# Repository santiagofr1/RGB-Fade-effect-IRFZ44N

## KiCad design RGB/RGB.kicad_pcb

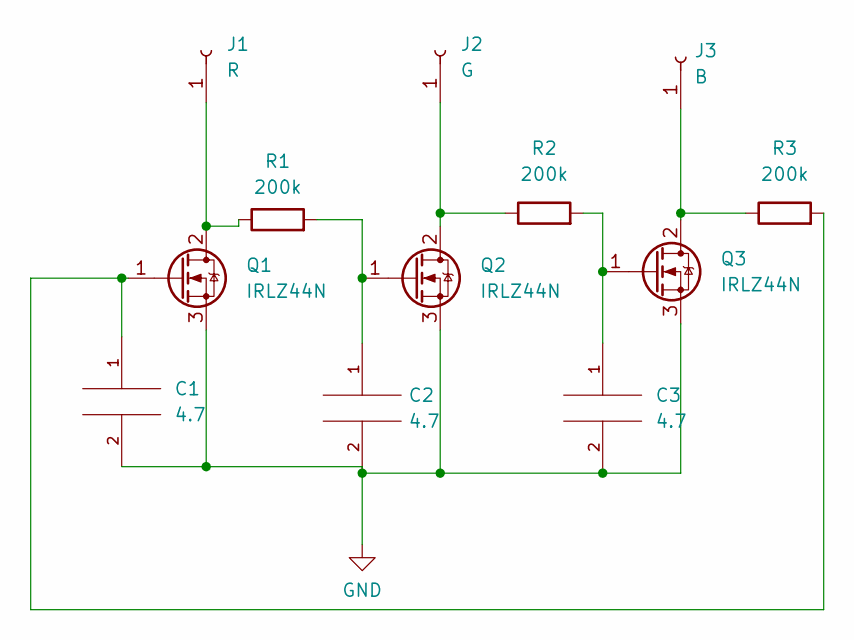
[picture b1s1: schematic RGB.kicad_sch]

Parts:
C1, C2, C3: 4.7; CP_Radial_D5.0mm_P2.00mm
J1: R; Pin_D1.0mm_L10.0mm
J2: G; Pin_D1.0mm_L10.0mm
J3: B; Pin_D1.0mm_L10.0mm
Q1, Q2, Q3: IRLZ44N; TO-220-3_Vertical
R1, R2, R3: 200k; R_Axial_DIN0207_L6.3mm_D2.5mm_P7.62mm_Horizontal

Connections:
GND: C1.2, C2.2, C3.2, Q1.3 (S), Q2.3 (S), Q3.3 (S); also elsewhere on the board
unnamed: C1.1, Q1.1 (G), R3.2
unnamed: C2.1, Q2.1 (G), R1.2
unnamed: C3.1, Q3.1 (G), R2.2
unnamed: J1.1, Q1.2 (D), R1.1
unnamed: J2.1, Q2.2 (D), R2.1
unnamed: J3.1, Q3.2 (D), R3.1

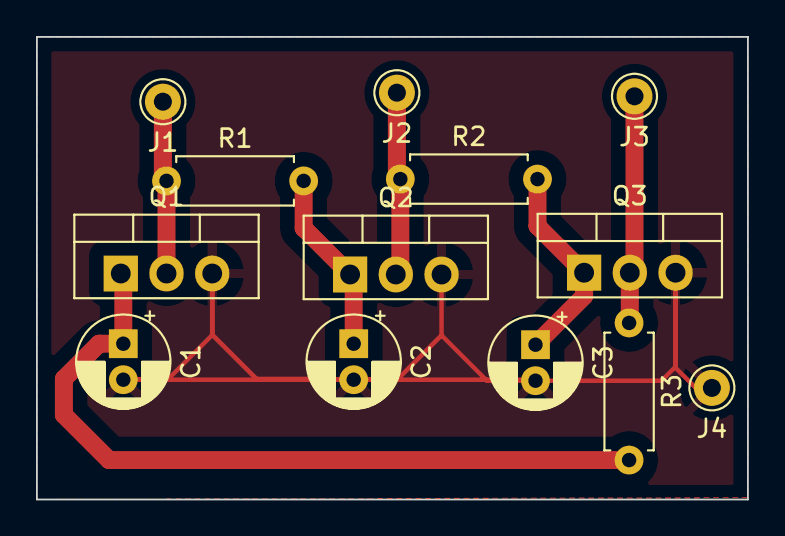
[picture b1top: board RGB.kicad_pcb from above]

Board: 2 copper layers, 39.5 x 25.7 mm, 13 parts (0 on the bottom side), 7 nets.

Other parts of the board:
J4: B; Pin_D1.0mm_L10.0mm

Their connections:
GND: J4.1; also elsewhere on the board
